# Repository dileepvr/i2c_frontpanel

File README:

---------------------------------------------------------------
i2c Frontpanel with 7-segment digits, pushbuttons, and two LEDs
---------------------------------------------------------------

Dumb frontpanel for small projects. Can be daisy-chained as long as
you do not populate all (except one) of the i2c pull-up resistors.

Powered by ATTiny88.

4-pin inter-header spacing is arduino compatible.

The PCBnew files are:

* 1x7seg_4btn.kicad_pcb (One 7-segment digit, four buttons, two LEDs)
* 2x7seg_4btn.kicad_pcb (Two 7-segment digits, four buttons, two LEDs)
* 4x7seg_6btn.kicad_pcb (Four 7-segment digits, six buttons, two LEDs)
* 4btn.kicad_pcb (Four buttons, two LEDs)
* 6btn.kicad_pcb (Six buttons, two LEDs)
* i2c_frontpanel.kicad_pcb (Same as 4x7seg_6btn.kicad_pcb)

Gerber files included for 4x7seg_6btn.kicad_pcb and
1x7seg_4btn.kicad_pcb designs.

The "firmware" folder contains the firmware for the ATTiny88.
Uses the ATTinyCore library: https://github.com/SpenceKonde/ATTinyCore

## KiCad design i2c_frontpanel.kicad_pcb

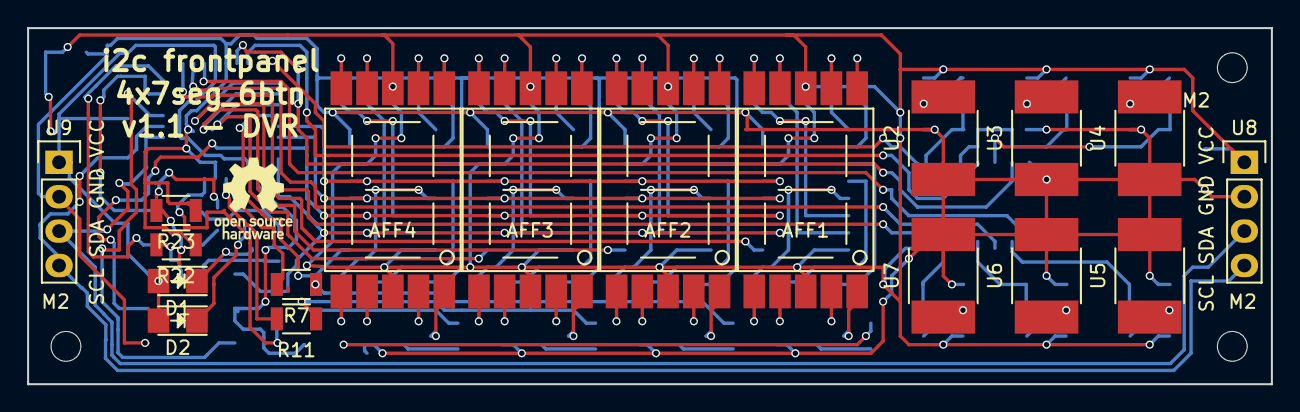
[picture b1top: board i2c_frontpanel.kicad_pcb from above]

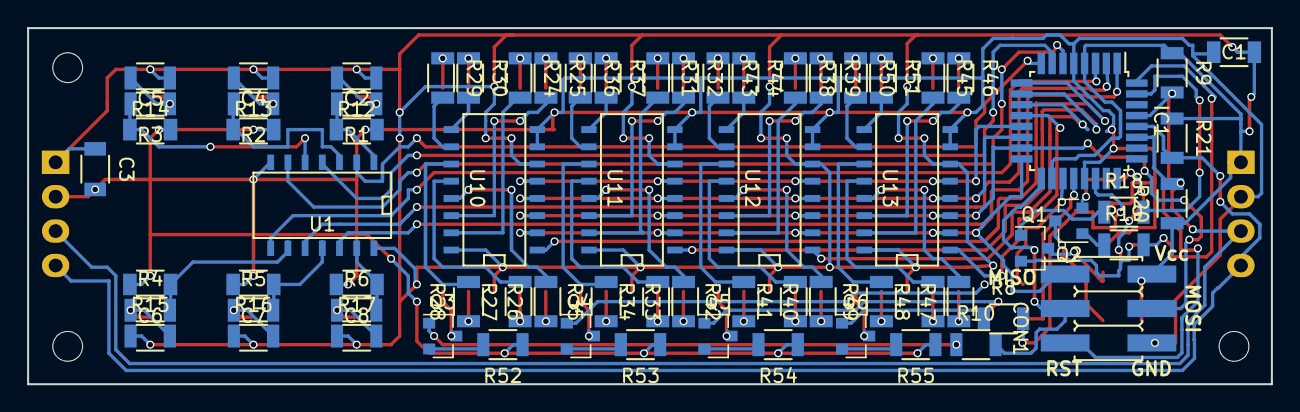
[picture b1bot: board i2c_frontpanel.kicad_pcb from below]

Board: 2 copper layers, 91.8 x 26.3 mm, 90 parts (72 on the bottom side), 111 nets.

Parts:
AFF1, AFF2, AFF3, AFF4: 7SEGMENTS; 7seg_LTS_4817CKR_P
C1, C2, C3, C4, C5, C6, C7, C8: 0.1uF; C_1206
CON1: AVR-ISP-6-DR; Pin_Header_Straight_SMT_02x03
D1, D2: LED; LED_1206
IC1: ATTINY88-A; TQFP-32_7x7mm_Pitch0.8mm
Q1, Q2, Q3, Q4, Q5, Q6: 2N7002; SOT-23
R1, R2, R3, R4, R5, R6, R9, R12, R13, R14, R15, R16, R17: 10k; R_1206
R7, R8, R10, R11, R18, R19: 100; R_1206
R20, R21: 4.7k; R_1206
R22, R23, R24, R25, R26, R27, R28, R29, R30, R31, R32, R33, R34, R35, R36, R37, R38, R39, R40, R41, R42, R43, R44, R45, R46, R47, R48, R49, R50, R51, R52, R53, R54, R55: 470; R_1206
U1: 74HC14D_653; SOIC-14_N
U2, U3, U4, U5, U6, U7: SW_SPST; R_2816
U8, U9: SCL SDA GND VCC; Pin_Header_Straight_1x04
U10, U11, U12, U13: MC14543B; SO-16-N

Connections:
/A: IC1.13, U10.5, U11.5, U12.5, U13.5
/B: CON1.4, IC1.15, U10.3, U11.3, U12.3, U13.3
/B1: C2.1, R1.2, U1.1
/B2: C4.1, R2.2, U1.3
/B3: C5.1, R3.2, U1.5
/B4: C6.1, R4.2, U1.9
/B5: C7.1, R5.2, U1.11
/B6: C8.1, R6.2, U1.13
/C: CON1.1, IC1.16, U10.2, U11.2, U12.2, U13.2
/D: IC1.14, U10.4, U11.4, U12.4, U13.4
/DP0: Q3.1, R10.1
/DP1: Q4.1, R7.1
/DP2: Q5.1, R11.1
/DP3: Q6.1, R8.1
/LD0: IC1.9, U10.1
/LD1: IC1.10, U11.1
/LD2: IC1.11, U12.1
/LD3: IC1.12, U13.1
/LED1: IC1.31, R18.2
/LED2: IC1.32, R19.2
/RST: CON1.5, IC1.29, R9.2
/S1: R1.1, R12.2, U2.2
/S2: R2.1, R13.2, U3.2
/S3: R3.1, R14.2, U4.2
/S4: R4.1, R15.2, U5.2
/S5: R5.1, R16.2, U6.2
/S6: R6.1, R17.2, U7.2
/SCK: CON1.3, IC1.17, R10.2
/SCL: IC1.28, R21.2, U8.4, U9.4
/SDA: IC1.27, R20.2, U8.3, U9.3
/SW1: IC1.8, U1.2
/SW2: IC1.7, U1.4
/SW3: IC1.6, U1.6
/SW4: IC1.3, U1.8
/SW5: IC1.2, U1.10
/SW6: IC1.1, U1.12
GND: C1.2, C2.2, C3.2, C4.2, C5.2, C6.2, C7.2, C8.2, CON1.6, IC1.5, IC1.21, R22.1, R23.1, R52.1, R53.1, R54.1, R55.1, U1.7, U2.1, U3.1, U4.1, U5.1, U6.1, U7.1, U8.2, U9.2, U10.7, U10.8, U11.7, U11.8, U12.7, U12.8, U13.7, U13.8
unnamed: AFF1.1, R26.1
unnamed: AFF1.2, R27.1
unnamed: AFF1.4, R28.1
unnamed: AFF1.5, Q3.3
unnamed: AFF1.6, R29.1
unnamed: AFF1.7, R30.1
unnamed: AFF1.9, R24.1
unnamed: AFF1.10, R25.1
unnamed: AFF2.1, R33.1
unnamed: AFF2.2, R34.1
unnamed: AFF2.4, R35.1
unnamed: AFF2.5, Q4.3
unnamed: AFF2.6, R36.1
unnamed: AFF2.7, R37.1
unnamed: AFF2.9, R31.1
unnamed: AFF2.10, R32.1
unnamed: AFF3.1, R40.1
unnamed: AFF3.2, R41.1
unnamed: AFF3.4, R42.1
unnamed: AFF3.5, Q5.3
unnamed: AFF3.6, R43.1
unnamed: AFF3.7, R44.1
unnamed: AFF3.9, R38.1
unnamed: AFF3.10, R39.1
unnamed: AFF4.1, R47.1
unnamed: AFF4.2, R48.1
unnamed: AFF4.4, R49.1
unnamed: AFF4.5, Q6.3
unnamed: AFF4.6, R50.1
unnamed: AFF4.7, R51.1
unnamed: AFF4.9, R45.1
unnamed: AFF4.10, R46.1
unnamed: D1.1, Q1.3
unnamed: D2.1, Q2.3
unnamed: IC1.19, R7.2
unnamed: IC1.20, R11.2
unnamed: IC1.22, R8.2
unnamed: Q1.1, R18.1
unnamed: Q1.2, R22.2
unnamed: Q2.1, R19.1
unnamed: Q2.2, R23.2
unnamed: Q3.2, R52.2
unnamed: Q4.2, R53.2
unnamed: Q5.2, R54.2
unnamed: Q6.2, R55.2
unnamed: R24.2, U10.15
unnamed: R25.2, U10.14
unnamed: R26.2, U10.13
unnamed: R27.2, U10.12
unnamed: R28.2, U10.11
unnamed: R29.2, U10.10
unnamed: R30.2, U10.9
unnamed: R31.2, U11.15
unnamed: R32.2, U11.14
unnamed: R33.2, U11.13
unnamed: R34.2, U11.12
unnamed: R35.2, U11.11
unnamed: R36.2, U11.10
unnamed: R37.2, U11.9
unnamed: R38.2, U12.15
unnamed: R39.2, U12.14
unnamed: R40.2, U12.13
unnamed: R41.2, U12.12
unnamed: R42.2, U12.11
unnamed: R43.2, U12.10
unnamed: R44.2, U12.9
unnamed: R45.2, U13.15
unnamed: R46.2, U13.14
unnamed: R47.2, U13.13
unnamed: R48.2, U13.12
unnamed: R49.2, U13.11
unnamed: R50.2, U13.10
unnamed: R51.2, U13.9
VCC: AFF1.3, AFF1.8, AFF2.3, AFF2.8, AFF3.3, AFF3.8, AFF4.3, AFF4.8, C1.1, C3.1, CON1.2, D1.2, D2.2, IC1.4, IC1.18, R9.1, R12.1, R13.1, R14.1, R15.1, R16.1, R17.1, R20.1, R21.1, U1.14, U8.1, U9.1, U10.6, U10.16, U11.6, U11.16, U12.6, U12.16, U13.6, U13.16

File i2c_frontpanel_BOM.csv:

Reference, Quantity, Value, Footprint,Part function,Mouser part #,Mouser link
AFF1 AFF2 AFF3 AFF4 ,4,7SEGMENTS,i2c_frontpanel:7seg_LTS_4817CKR_P,7 segment digit,859-LTS-4817CKR-P,https://www.mouser.com/ProductDetail/lite-on/lts-4817ckr-p/?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
C1 C2 C3 C4 C5 C6 C7 C8 ,8,0.1uF,Capacitors_SMD:C_1206,Capacitor,710-885012208009,https://www.mouser.com/ProductDetail/wurth-electronics/88501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
CON1 ,1,AVR-ISP-6-DR,Pin_Headers:Pin_Header_Straight_SMT_02x03,2x3 vertical smd header pins,538-15-91-2060 ,https://www.mouser.com/ProductDetail/molex/15-91-2060/?qs=TE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
D1 D2 ,2,LED,LEDs:LED_1206,Colored status LEDs,743-S126ATG,https://www.mouser.com/ProductDetail/inolux/in-s126atg/?qs=u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
IC1 ,1,ATTINY88-A,Housings_QFP:TQFP-32_7x7mm_Pitch0.8mm,ATTINY88 Microcontroller,556-ATTINY88-MMUR,https://www.mouser.com/ProductDetail/microchip/attiny88-mmur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
Q1 Q2 Q3 Q4 Q5 Q6 ,6,2N7002,TO_SOT_Packages_SMD:SOT-23,N-MOSFET,512-2N7002L,https://www.mouser.com/ProductDetail/on-semiconductor/2n7002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
R20 R21 ,2,4.7k,Resistors_SMD:R_1206,Resistor,603-RC0402FR-104K7L ,https://www.mouser.com/ProductDetail/yageo/rc0402fr-104k7l/?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
R22 R23 R24 R25 R26 R27 R28 R29 R30 R31 R32 R33 R34 R35 R36 R37 R38 R39 R40 R41 R42 R43 R44 R45 R46 R47 R48 R49 R50 R51 R52 R53 R54 R55 ,34,470,Resistors_SMD:R_1206,Resistor,603-RC0402FR-13200RL ,https://www.mouser.com/ProductDetail/yageo/rc0402fr-13200rl/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
R10 R11 R18 R19 R7 R8 ,6,100,Resistors_SMD:R_1206,Resistor,603-RC0402FR-13200RL ,https://www.mouser.com/ProductDetail/yageo/rc0402fr-13200rl/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
R1 R12 R13 R14 R15 R16 R17 R2 R3 R4 R5 R6 R9 ,13,10k,Resistors_SMD:R_1206,Resistor,667-ERJ-8ENF1002V ,https://www.mouser.com/ProductDetail/panasonic/erj-8enf1002v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
U1 ,1,74HC14D_653,SMD_Packages:SOIC-14_N,Hex inverter buffer for debouncing,771-74HC14D-T,https://www.mouser.com/ProductDetail/nexperia/74hc14d653/?qs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
U10 U11 U12 U13 ,4,MC14543B,SMD_Packages:SO-16-N,BCD-to-7-segment decoder,863-MC14543BDR2G,https://www.mouser.com/ProductDetail/on-semiconductor/mc1454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
U2 U3 U4 U5 U6 U7 ,6,SW_SPST,Resistors_SMD:R_2816,Pushbuttons,688-SKPSAAE010,https://www.mouser.com/ProductDetail/alps/skpsaae010/?qs=AQl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
U8 U9 ,2,I2C_4PINS,Pin_Headers:Pin_Header_Straight_1x04,Header pins,649-68001-236HLF ,https://www.mouser.com/ProductDetail/fci-amphenol/68001-236h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

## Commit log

2018-09-01 major components are in the schematic
2018-09-03 Schematic done.
2018-09-05 Footprints done. LICENSE now CERN open hardware license.
2018-09-08 PCB routing done.
2018-09-10 gerbers done.
2018-09-10 removed backup file
2018-09-10 Moved oshw logo
2018-09-10 Moved header pins on 1x7seg_4btn version to match height on both sides
2018-09-11 Headers aligned better
2018-09-11 Added new pcb layouts
2018-09-22 Added BOM. Moved i2c pin designations to silkscreen.
2019-03-09 v1.1 fixed 74HC14 bottom-row button pin mappings.
2019-03-09 Added AttinyCore fimrware and i2c_master firmware for testing.
2019-03-09 Firmare and README file added
